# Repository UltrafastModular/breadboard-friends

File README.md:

breadboard-friends
==================

A collection of cute breakout boards riding solderless breadboards, mostly for analog audio works

These PCB layouts and schematics are released under a Creative Commons cc-by-sa
3.0 license.

Original design by émilie gillet
Design revisions by Gareth Johnson
Converted to KiCad and further revision by Nathan Schenk

NOTE: This is a forked version of breadboard-friends and adds two addition BBFs, one using Thonkiconn 3.5mm Jacks (bbf-thonkjacks) and another providing eurorack header with polarity protection for providing eurorack power to your breadboard from euro bus (bbf-europower).
NOTE: This version converts the project from Eagle to KiCad and footprint updates to jacks, including oval holes

BBF-EUROPOWER Bill Of Materials (BOM)

- 2x 200ma PTC Poly Fuse or equivalent (or jumper wires if no fuse is required);
- 2x 10uF 25V Electrolytic Caps;
- 2x 1N5818 diodes or equivalent;
- 2x Ferrite Beads;
- 4x 10 Pin DIL male headers.

BBF-THONKJACKS Bill Of Materials (BOM)

- 4x Thonkiconn Jacks;
- 1x 8 pin SIL female header;
- 2x 10 pin DIL male headers.

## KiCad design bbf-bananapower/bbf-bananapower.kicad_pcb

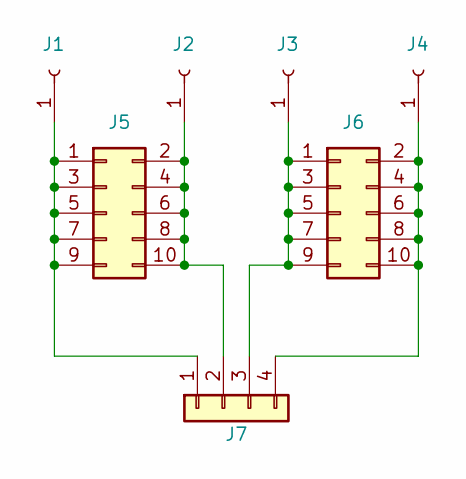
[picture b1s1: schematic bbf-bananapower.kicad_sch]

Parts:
J1, J2, J3, J4: Conn_01x01_Female; Banana_Cliff_S16N-PC
J5, J6: Conn_02x05_Counter_Clockwise; PinSocket_2x05_P2.54mm_Vertical
J7: Conn_01x04; PinSocket_1x04_P2.54mm_Vertical

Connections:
unnamed: J1.1, J5.1, J5.3, J5.5, J5.7, J5.9, J7.1
unnamed: J2.1, J5.2, J5.4, J5.6, J5.8, J5.10, J7.2
unnamed: J3.1, J6.1, J6.3, J6.5, J6.7, J6.9, J7.3
unnamed: J4.1, J6.2, J6.4, J6.6, J6.8, J6.10, J7.4

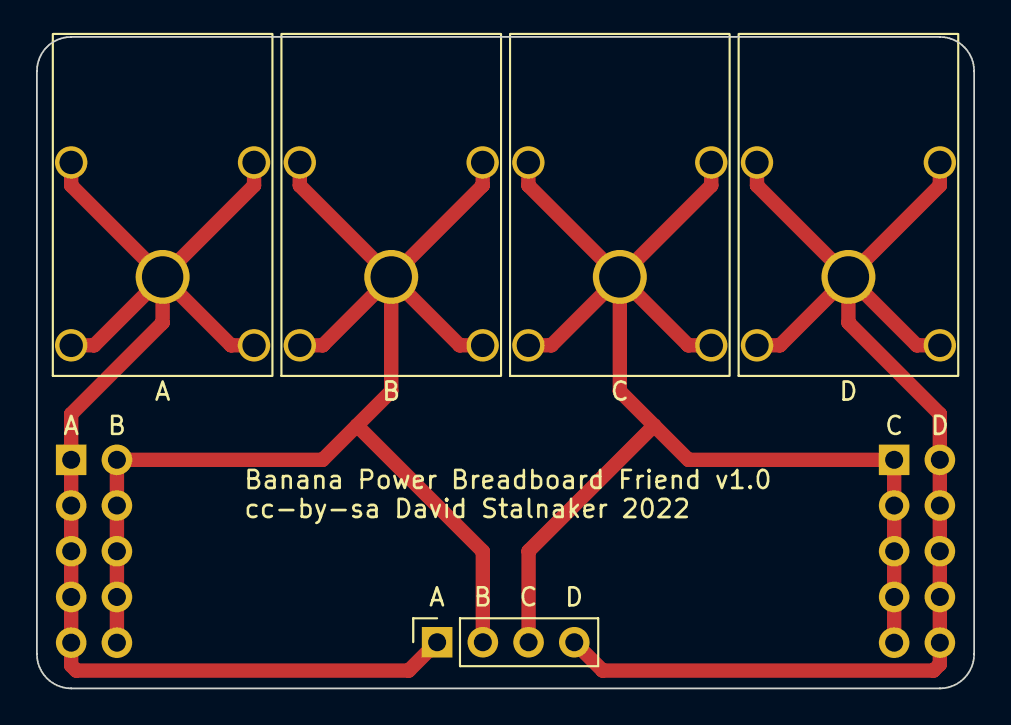
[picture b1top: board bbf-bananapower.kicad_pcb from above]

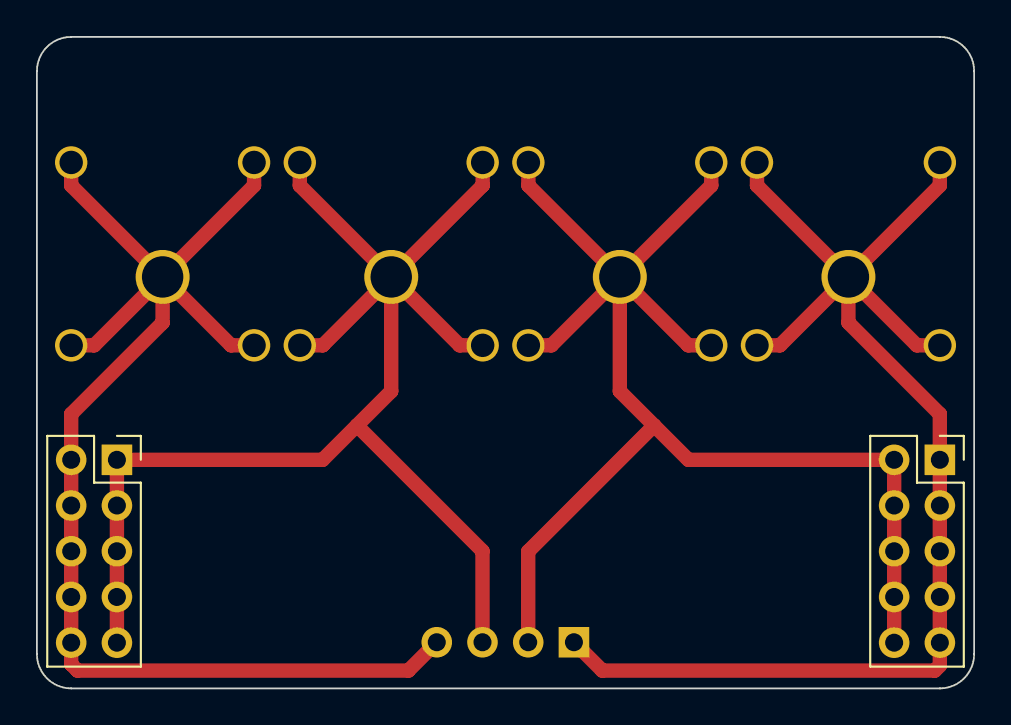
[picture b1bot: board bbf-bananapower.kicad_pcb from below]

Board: 2 copper layers, 52.1 x 36.2 mm, 7 parts (2 on the bottom side), 4 nets.

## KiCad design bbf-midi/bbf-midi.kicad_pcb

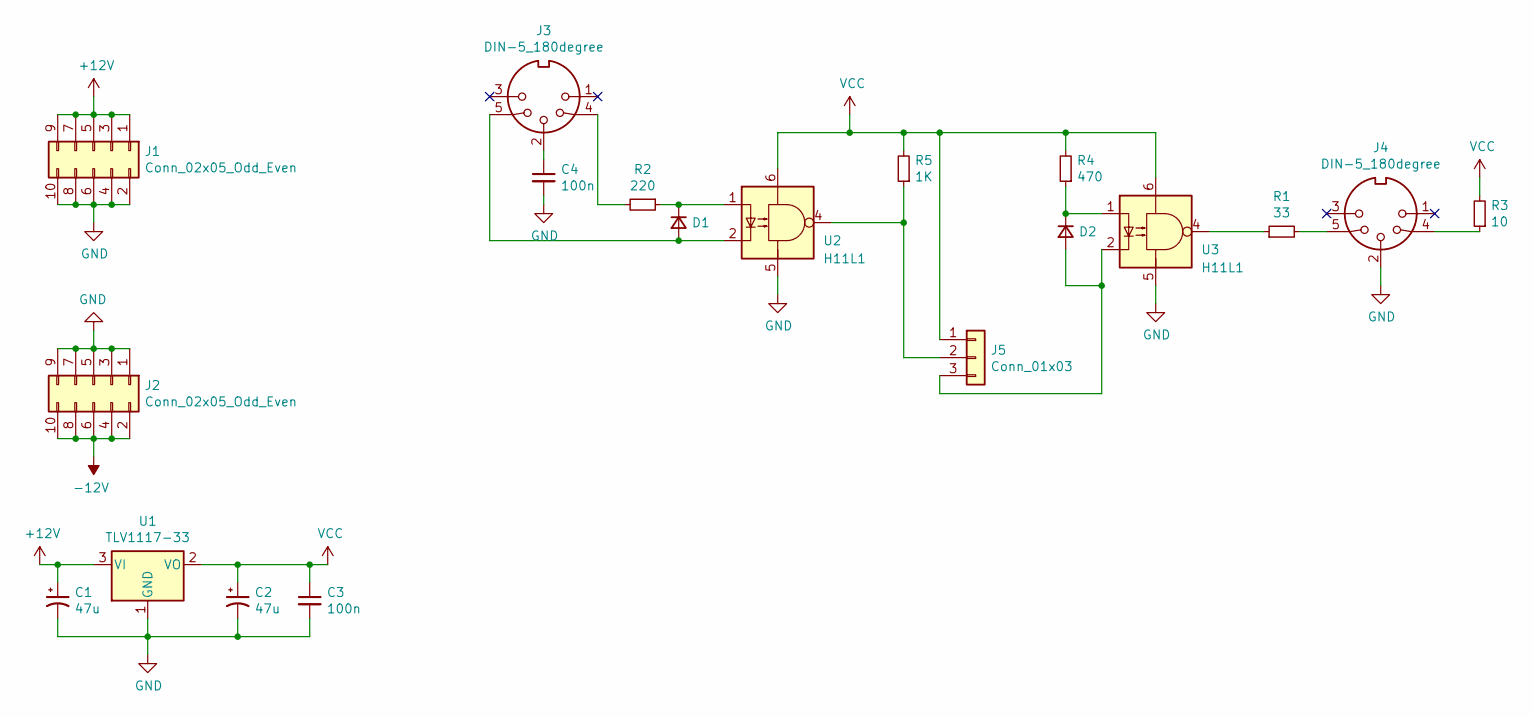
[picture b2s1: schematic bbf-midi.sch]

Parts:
C1, C2: 47u; CP_Radial_D5.0mm_P2.50mm
C3, C4: 100n; C_Disc_D3.0mm_W2.0mm_P2.50mm
D1, D2: D_Small; D_DO-35_SOD27_P7.62mm_Horizontal
J1, J2: Conn_02x05_Odd_Even; PinHeader_2x05_P2.54mm_Vertical
J3, J4: DIN-5_180degree; DIN_5_CUI_SDF-50J
J5: Conn_01x03; PinSocket_1x03_P2.54mm_Vertical
R1: 33; R_Axial_DIN0207_L6.3mm_D2.5mm_P7.62mm_Horizontal
R2: 220; R_Axial_DIN0207_L6.3mm_D2.5mm_P7.62mm_Horizontal
R3: 10; R_Axial_DIN0207_L6.3mm_D2.5mm_P7.62mm_Horizontal
R4: 470; R_Axial_DIN0207_L6.3mm_D2.5mm_P7.62mm_Horizontal
R5: 1K; R_Axial_DIN0207_L6.3mm_D2.5mm_P7.62mm_Horizontal
U1: TLV1117-33; TO-220-3_Vertical
U2, U3: H11L1; DIP-6_W7.62mm_Socket

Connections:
+12V: C1.1, J1.1, J1.3, J1.5, J1.7, J1.9, U1.3 (VI)
-12V: J2.2, J2.4, J2.6, J2.8, J2.10
GND: C1.2, C2.2, C3.2, C4.2, J1.2, J1.4, J1.6, J1.8, J1.10, J2.1, J2.3, J2.5, J2.7, J2.9, J4.2, U1.1 (GND), U2.5, U3.5
unnamed: C4.1, J3.2
unnamed: D1.1 (K), R2.1, U2.1
unnamed: D1.2 (A), J3.5, U2.2
unnamed: D2.1 (K), R4.1, U3.1
unnamed: D2.2 (A), J5.3, U3.2
unnamed: J3.4, R2.2
unnamed: J4.4, R3.1
unnamed: J4.5, R1.2
unnamed: J5.2, R5.1, U2.4
unnamed: R1.1, U3.4
VCC: C2.1, C3.1, J5.1, R3.2, R4.2, R5.2, U1.2 (VO), U2.6, U3.6

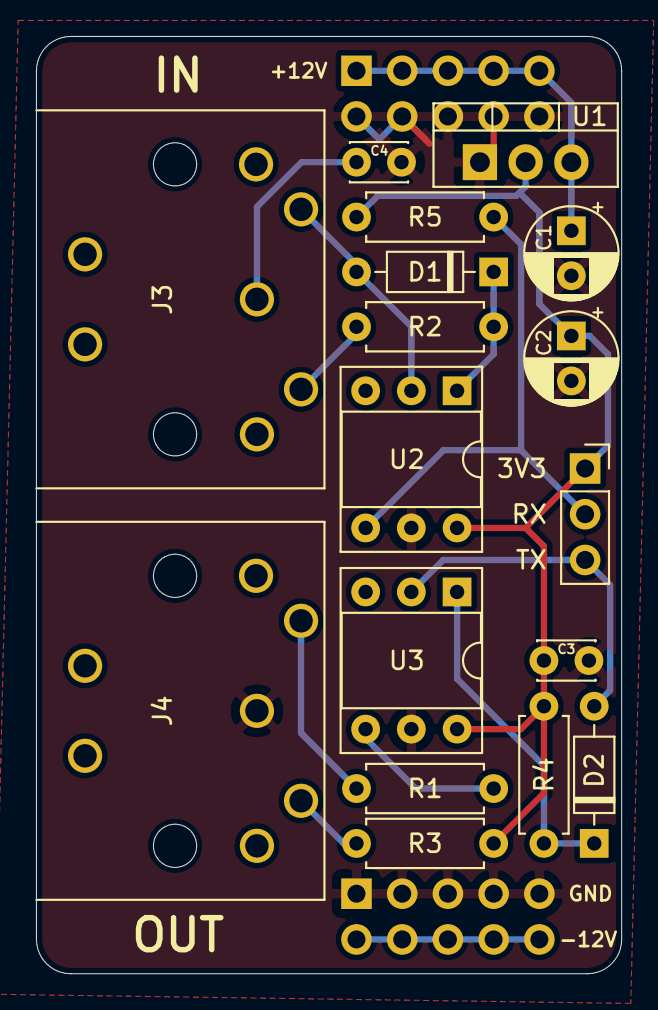
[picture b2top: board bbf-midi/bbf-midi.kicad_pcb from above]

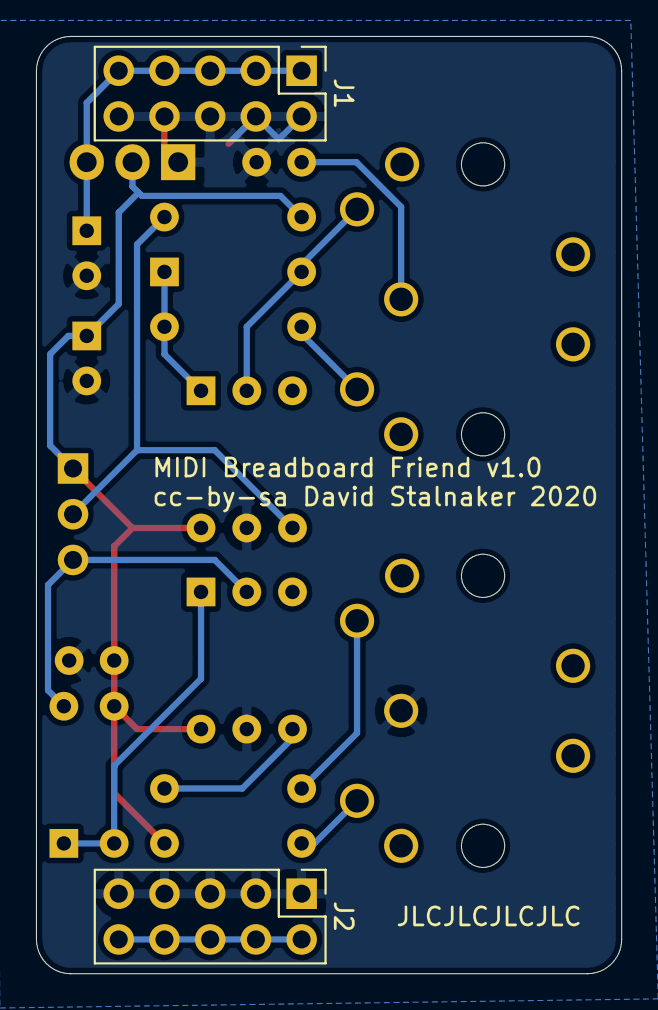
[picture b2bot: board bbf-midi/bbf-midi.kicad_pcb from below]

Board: 2 copper layers, 32.5 x 52.1 mm, 19 parts (2 on the bottom side), 14 nets.

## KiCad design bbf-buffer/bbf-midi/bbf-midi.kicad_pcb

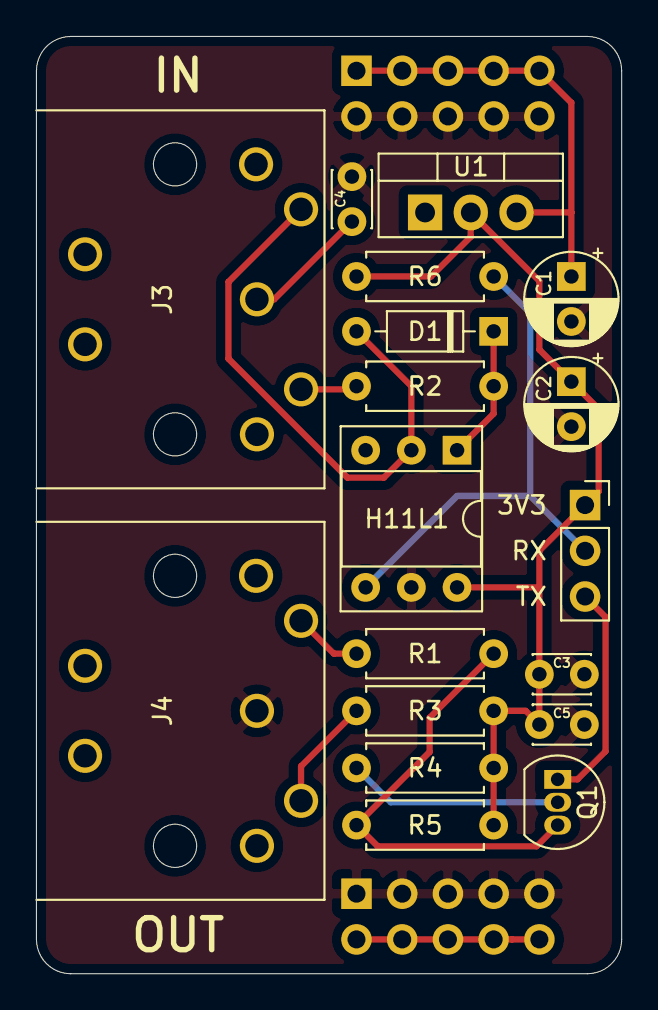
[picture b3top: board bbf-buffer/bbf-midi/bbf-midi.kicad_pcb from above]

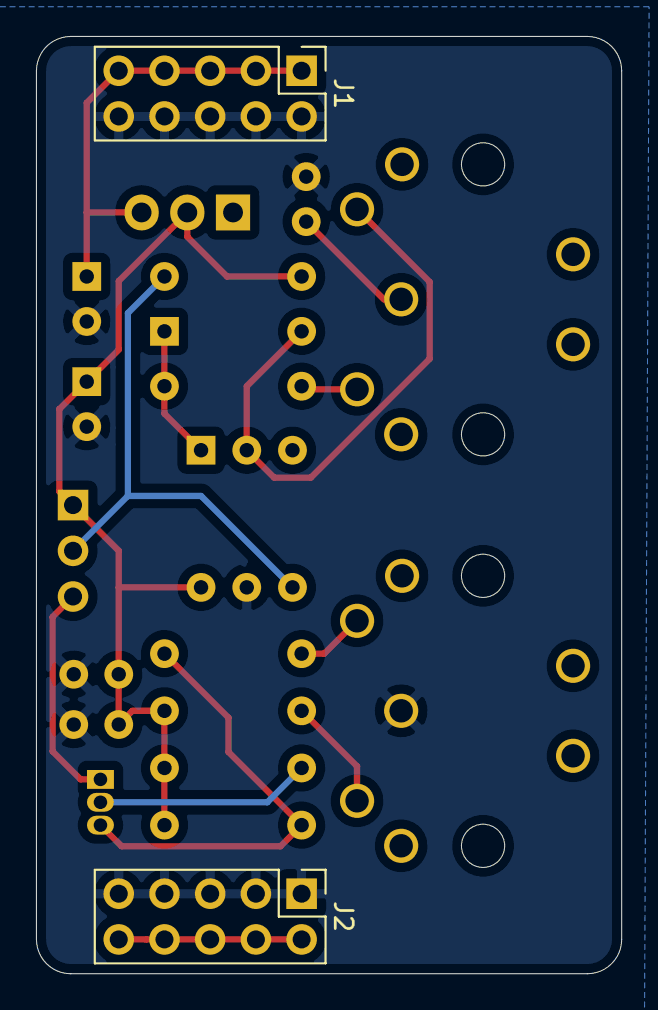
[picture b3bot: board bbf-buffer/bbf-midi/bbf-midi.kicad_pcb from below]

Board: 2 copper layers, 32.5 x 52.1 mm, 20 parts (2 on the bottom side), 14 nets.

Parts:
C1, C2: 47u; CP_Radial_D5.0mm_P2.50mm
C3, C4, C5: 100n; C_Disc_D3.0mm_W2.0mm_P2.50mm
D1: D_Small; D_DO-35_SOD27_P7.62mm_Horizontal
H11L1: H11L1; DIP-6_W7.62mm_Socket
J1, J2: Conn_02x05_Odd_Even; PinHeader_2x05_P2.54mm_Vertical
J3, J4: DIN-5_180degree; DIN_5_CUI_SDF-50J
J5: Conn_01x03; PinSocket_1x03_P2.54mm_Vertical
Q1: 2N3904; TO-92_Inline
R1: 33; R_Axial_DIN0207_L6.3mm_D2.5mm_P7.62mm_Horizontal
R2: 220; R_Axial_DIN0207_L6.3mm_D2.5mm_P7.62mm_Horizontal
R3: 10; R_Axial_DIN0207_L6.3mm_D2.5mm_P7.62mm_Horizontal
R4, R5, R6: 1K; R_Axial_DIN0207_L6.3mm_D2.5mm_P7.62mm_Horizontal
U1: TLV1117-33; TO-220-3_Vertical

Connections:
+12V: C1.1, J1.1, J1.3, J1.5, J1.7, J1.9, U1.3
-12V: J2.2, J2.4, J2.6, J2.8, J2.10
GND: C1.2, C2.2, C3.2, C4.2, C5.2, H11L1.5, J1.2, J1.4, J1.6, J1.8, J1.10, J2.1, J2.3, J2.5, J2.7, J2.9, J4.2
unnamed: C4.1, J3.2
unnamed: D1.1, H11L1.1, R2.1
unnamed: D1.2, H11L1.2, J3.5
unnamed: J3.4, R2.2
unnamed: J4.4, R3.1
unnamed: J4.5, R1.1
unnamed: H11L1.4, J5.2, R6.1
unnamed: J5.3, Q1.1
unnamed: Q1.2, R4.1
unnamed: Q1.3, R1.2, R5.1
VCC: C2.1, C3.1, C5.1, H11L1.6, J5.1, R3.2, R4.2, R5.2, R6.2, U1.2

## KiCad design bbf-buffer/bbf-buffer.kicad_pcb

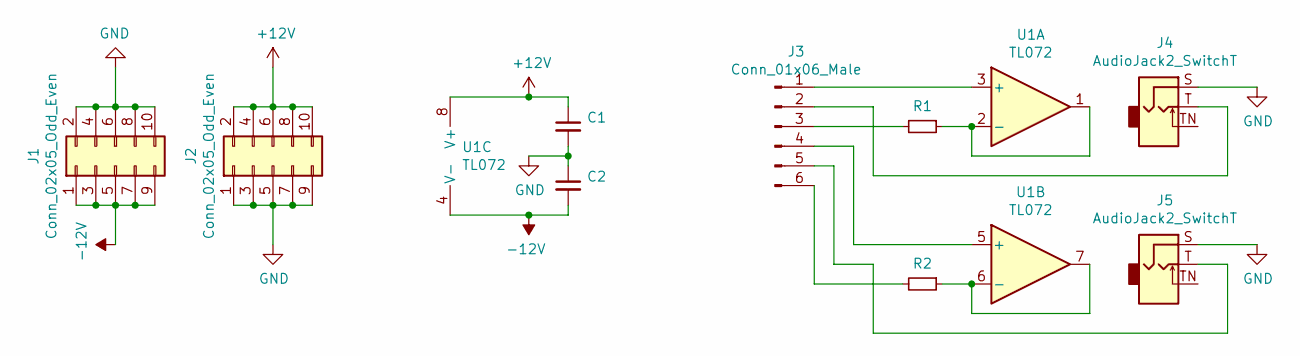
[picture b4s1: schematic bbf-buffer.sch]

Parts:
C1, C2: C_Small; C_Disc_D3.0mm_W1.6mm_P2.50mm
J1, J2: Conn_02x05_Odd_Even; PinHeader_2x05_P2.54mm_Vertical
J3: Conn_01x06_Male; PinHeader_1x06_P2.54mm_Vertical
J4, J5: AudioJack2_SwitchT; Thonkiconn_Tight
R1, R2: R_Small; R_Axial_DIN0207_L6.3mm_D2.5mm_P7.62mm_Horizontal
U1: TL072; DIP-8_W7.62mm_Socket

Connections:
+12V: C1.1, J2.2, J2.4, J2.6, J2.8, J2.10, U1.8 (V+); also elsewhere on the board
-12V: C2.2, J1.1, J1.3, J1.5, J1.7, J1.9, U1.4 (V-); also elsewhere on the board
GND: C1.2, C2.1, J1.2, J1.4, J1.6, J1.8, J1.10, J2.1, J2.3, J2.5, J2.7, J2.9, J4.S, J5.S
unnamed 3: J3.1, U1.3 (+); also elsewhere on the board
unnamed: J3.2, J4.T
unnamed: J3.3, R1.2
unnamed 6: J3.4, U1.5 (+); also elsewhere on the board
unnamed: J3.5, J5.T
unnamed: J3.6, R2.2
unnamed 9: R1.1, U1.1, U1.2 (-); also elsewhere on the board
unnamed 10: R2.1, U1.6 (-), U1.7; also elsewhere on the board

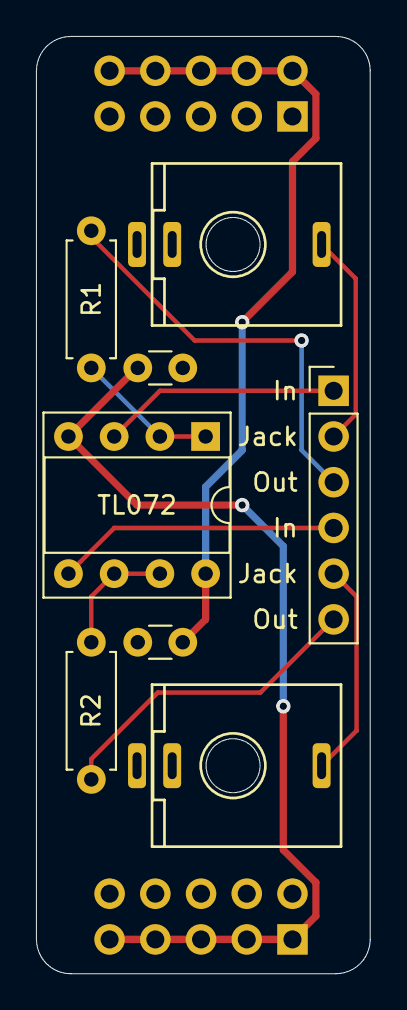
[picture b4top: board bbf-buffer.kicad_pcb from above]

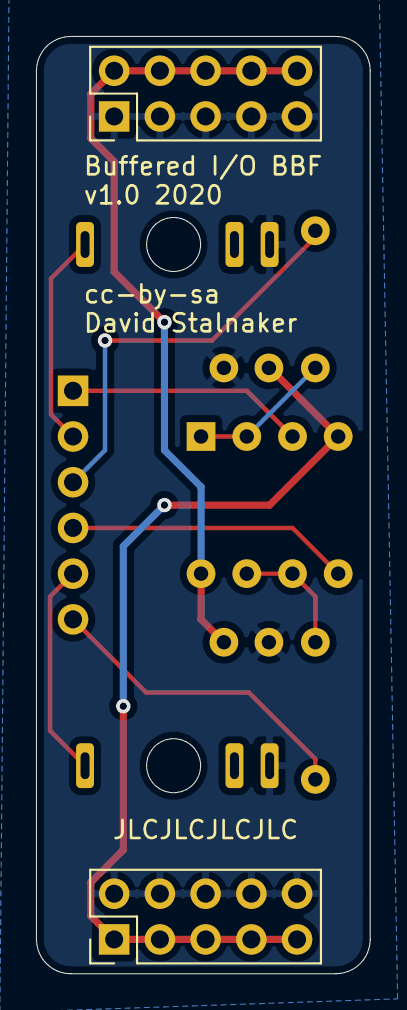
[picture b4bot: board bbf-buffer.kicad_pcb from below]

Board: 2 copper layers, 18.5 x 52.1 mm, 10 parts (2 on the bottom side), 11 nets.

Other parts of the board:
TL072: TL072; DIP-8_W7.62mm_Socket

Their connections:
+12V: TL072.8; also elsewhere on the board
-12V: TL072.4; also elsewhere on the board
unnamed 3: TL072.3; also elsewhere on the board
unnamed 6: TL072.5; also elsewhere on the board
unnamed 9: TL072.1, TL072.2; also elsewhere on the board
unnamed 10: TL072.6, TL072.7; also elsewhere on the board

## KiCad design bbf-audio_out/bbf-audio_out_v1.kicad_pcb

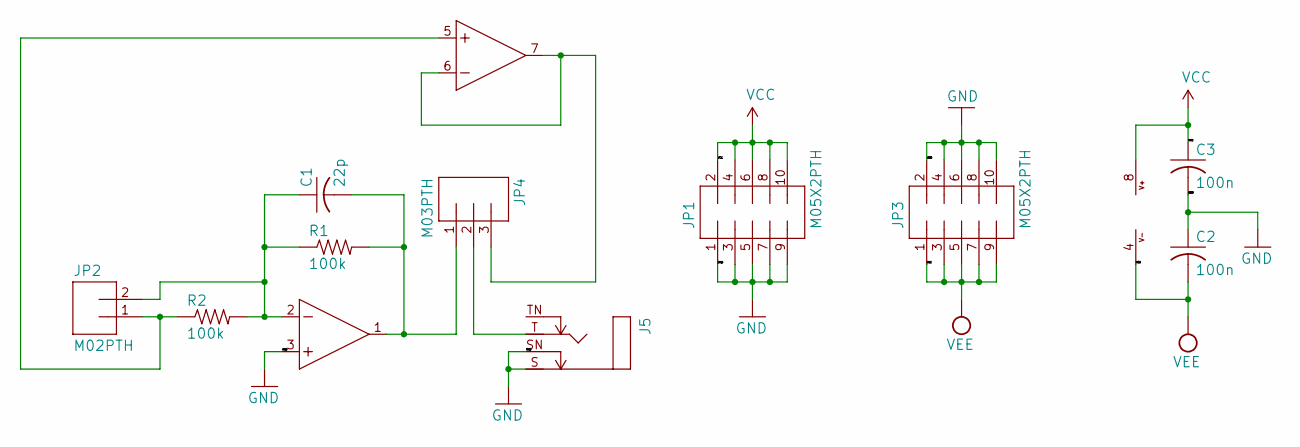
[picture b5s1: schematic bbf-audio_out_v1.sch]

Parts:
C1: 22p; C025-025X050
C2, C3: 100n; C025-025X050
IC1: TL072P; DIL08
J5: MONOSWSLIM; NRJ4HF
JP1, JP3: M05X2PTH; AVR_ICSP
JP2: M02PTH; 1X02
JP4: M03PTH; 1X03
R1, R2: 100k; 0204_7

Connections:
GND: C2.1, C3.2, IC1.3 (+IN), J5.S, J5.SN, JP1.1, JP1.3, JP1.5, JP1.7, JP1.9, JP3.2, JP3.4, JP3.6, JP3.8, JP3.10
unnamed: C1.1, IC1.2 (-IN), JP2.2, R1.1, R2.2
unnamed: C1.2, IC1.1 (OUT), JP4.1, R1.2
unnamed: IC1.5 (+IN), JP2.1, R2.1
unnamed: IC1.6 (-IN), IC1.7 (OUT), JP4.3
unnamed: J5.T, JP4.2
VCC: C3.1, IC1.8 (V+), JP1.2, JP1.4, JP1.6, JP1.8, JP1.10
VEE: C2.2, IC1.4 (V-), JP3.1, JP3.3, JP3.5, JP3.7, JP3.9

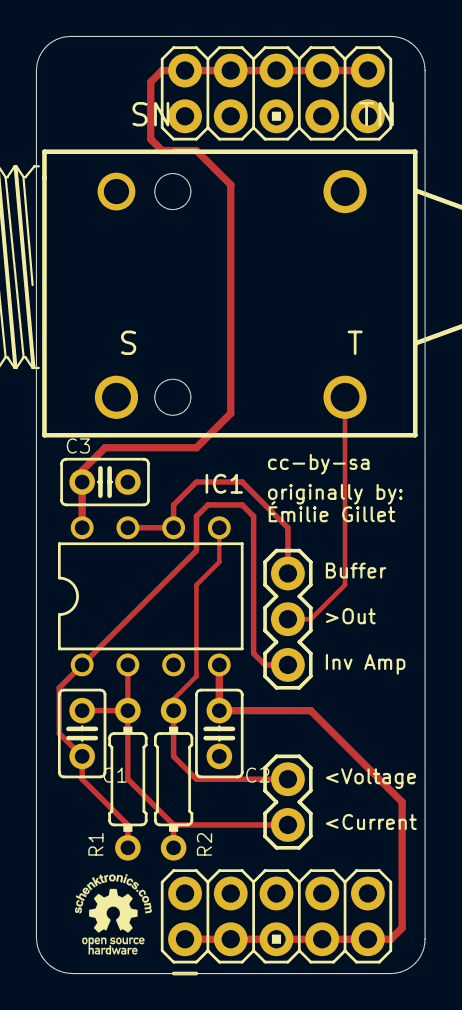
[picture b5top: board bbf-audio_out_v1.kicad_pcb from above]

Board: 2 copper layers, 21.6 x 52.1 mm, 11 parts (0 on the bottom side), 8 nets.

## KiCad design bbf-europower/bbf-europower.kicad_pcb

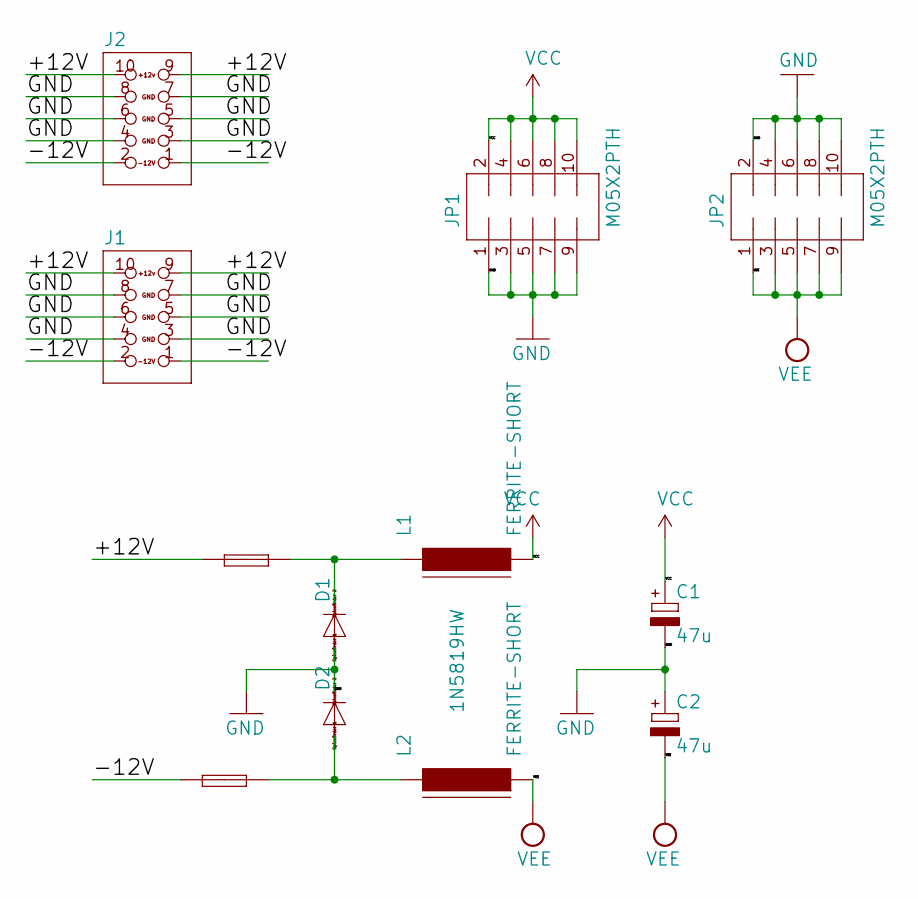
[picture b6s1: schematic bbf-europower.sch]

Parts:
+FUSE1: +FUSE; C050H075X075
-FUSE1: -FUSE; C050H075X075
C1, C2: 47u; E2-5
D1, D2: 1N5819HW; DO35-7
J1, J2: CON_HEADER_2X05-PTH; M2X5
JP1, JP2: M05X2PTH; AVR_ICSP
L1, L2: FERRITE-SHORT; FBS

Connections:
/+12V: +FUSE1.1, J1.9, J1.10, J2.9, J2.10
/-12V: -FUSE1.1, J1.1, J1.2, J2.1, J2.2
GND: C1.-, C2.+, D1.A, D2.C, J1.3, J1.4, J1.5, J1.6, J1.7, J1.8, J2.3, J2.4, J2.5, J2.6, J2.7, J2.8, JP1.1, JP1.3, JP1.5, JP1.7, JP1.9, JP2.2, JP2.4, JP2.6, JP2.8, JP2.10
unnamed: +FUSE1.2, D1.C, L1.1
unnamed: -FUSE1.2, D2.A, L2.1
VCC: C1.+, JP1.2, JP1.4, JP1.6, JP1.8, JP1.10, L1.2
VEE: C2.-, JP2.1, JP2.3, JP2.5, JP2.7, JP2.9, L2.2

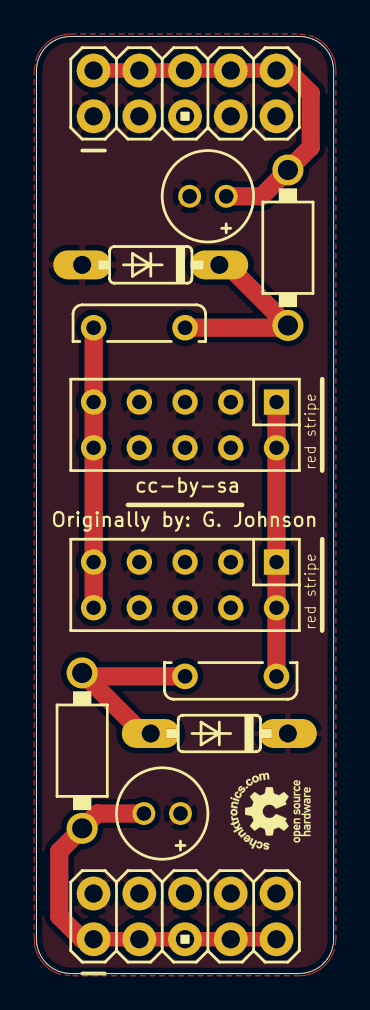
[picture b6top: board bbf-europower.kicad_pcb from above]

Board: 2 copper layers, 16.5 x 52.1 mm, 12 parts (0 on the bottom side), 7 nets.

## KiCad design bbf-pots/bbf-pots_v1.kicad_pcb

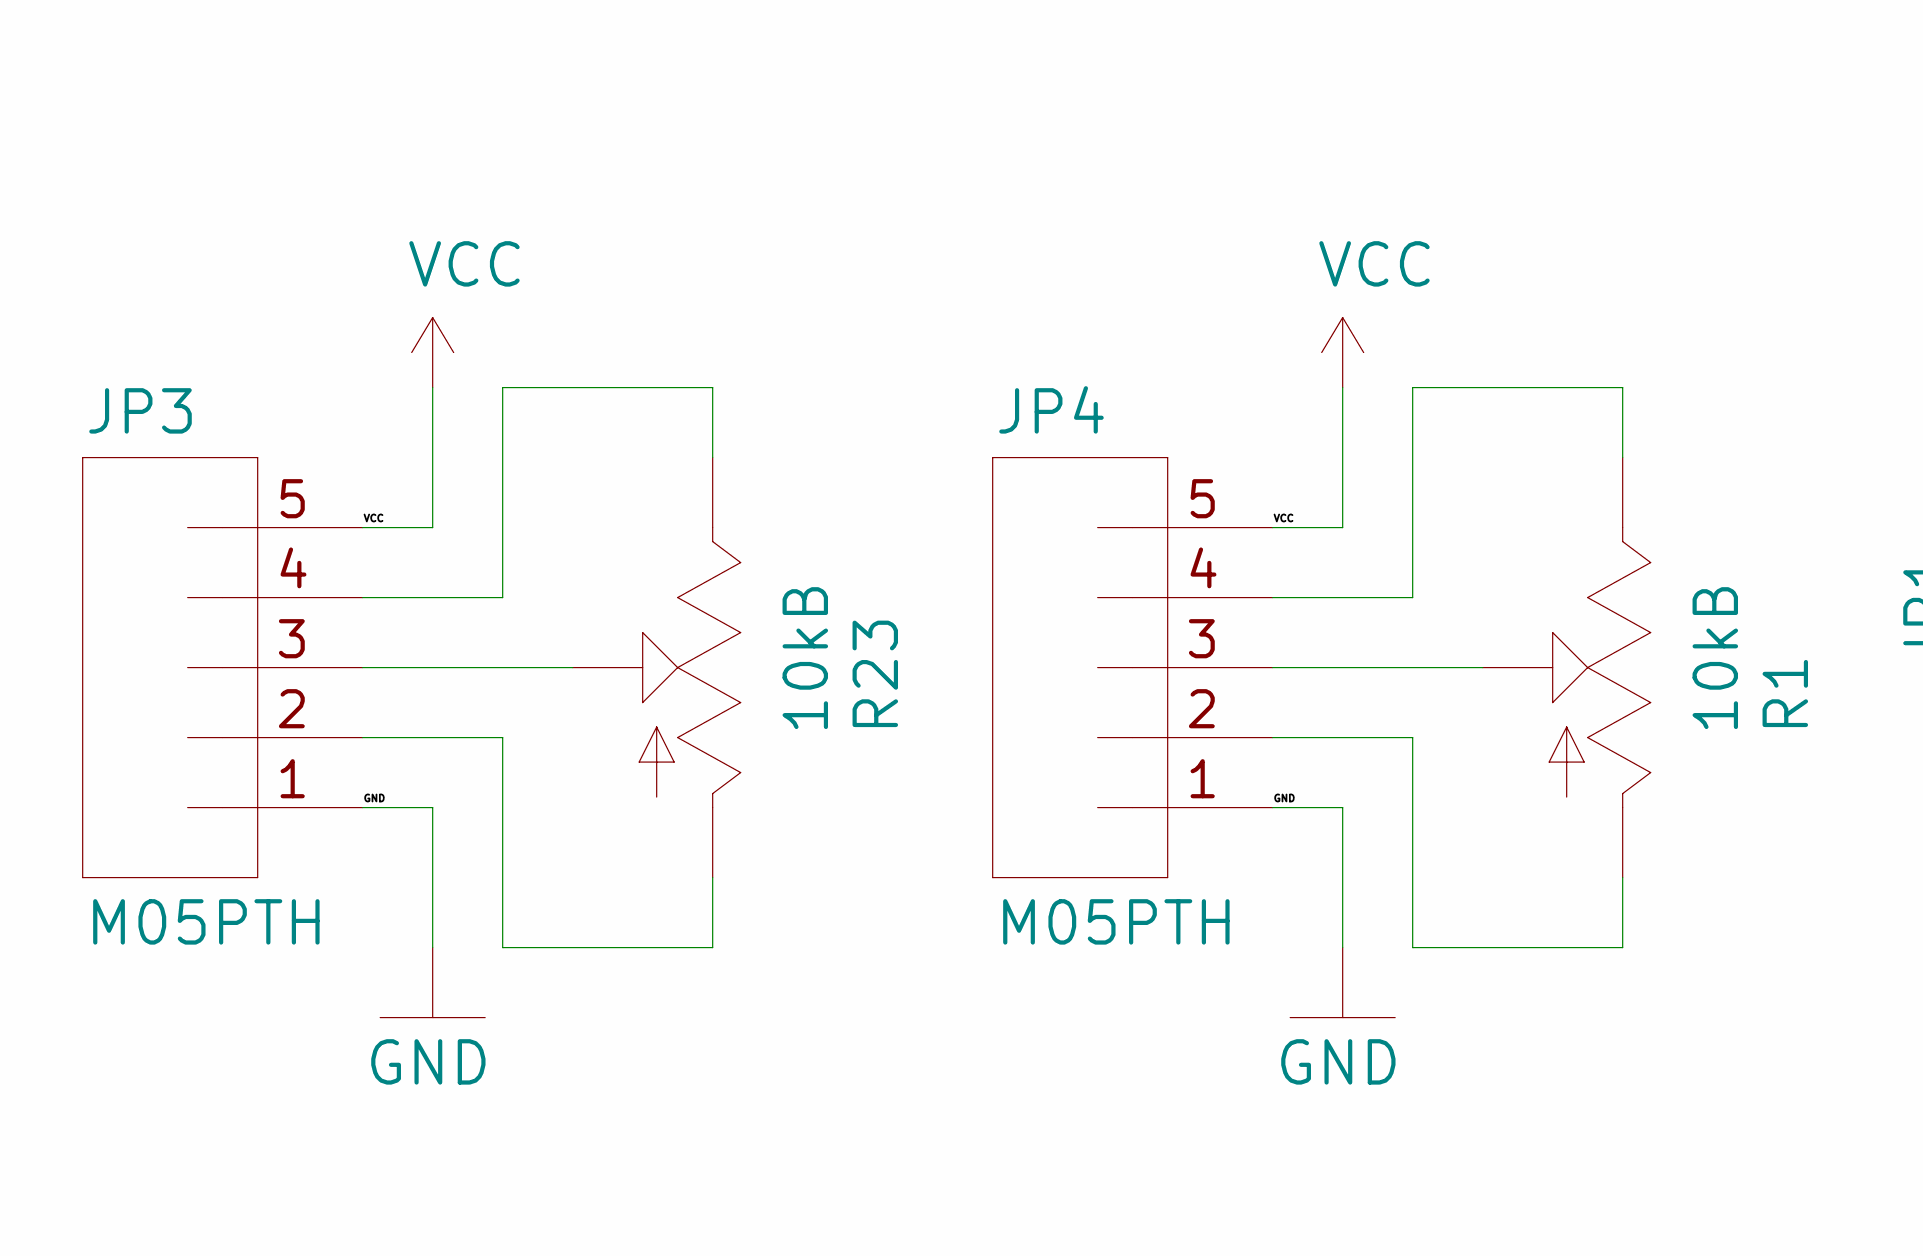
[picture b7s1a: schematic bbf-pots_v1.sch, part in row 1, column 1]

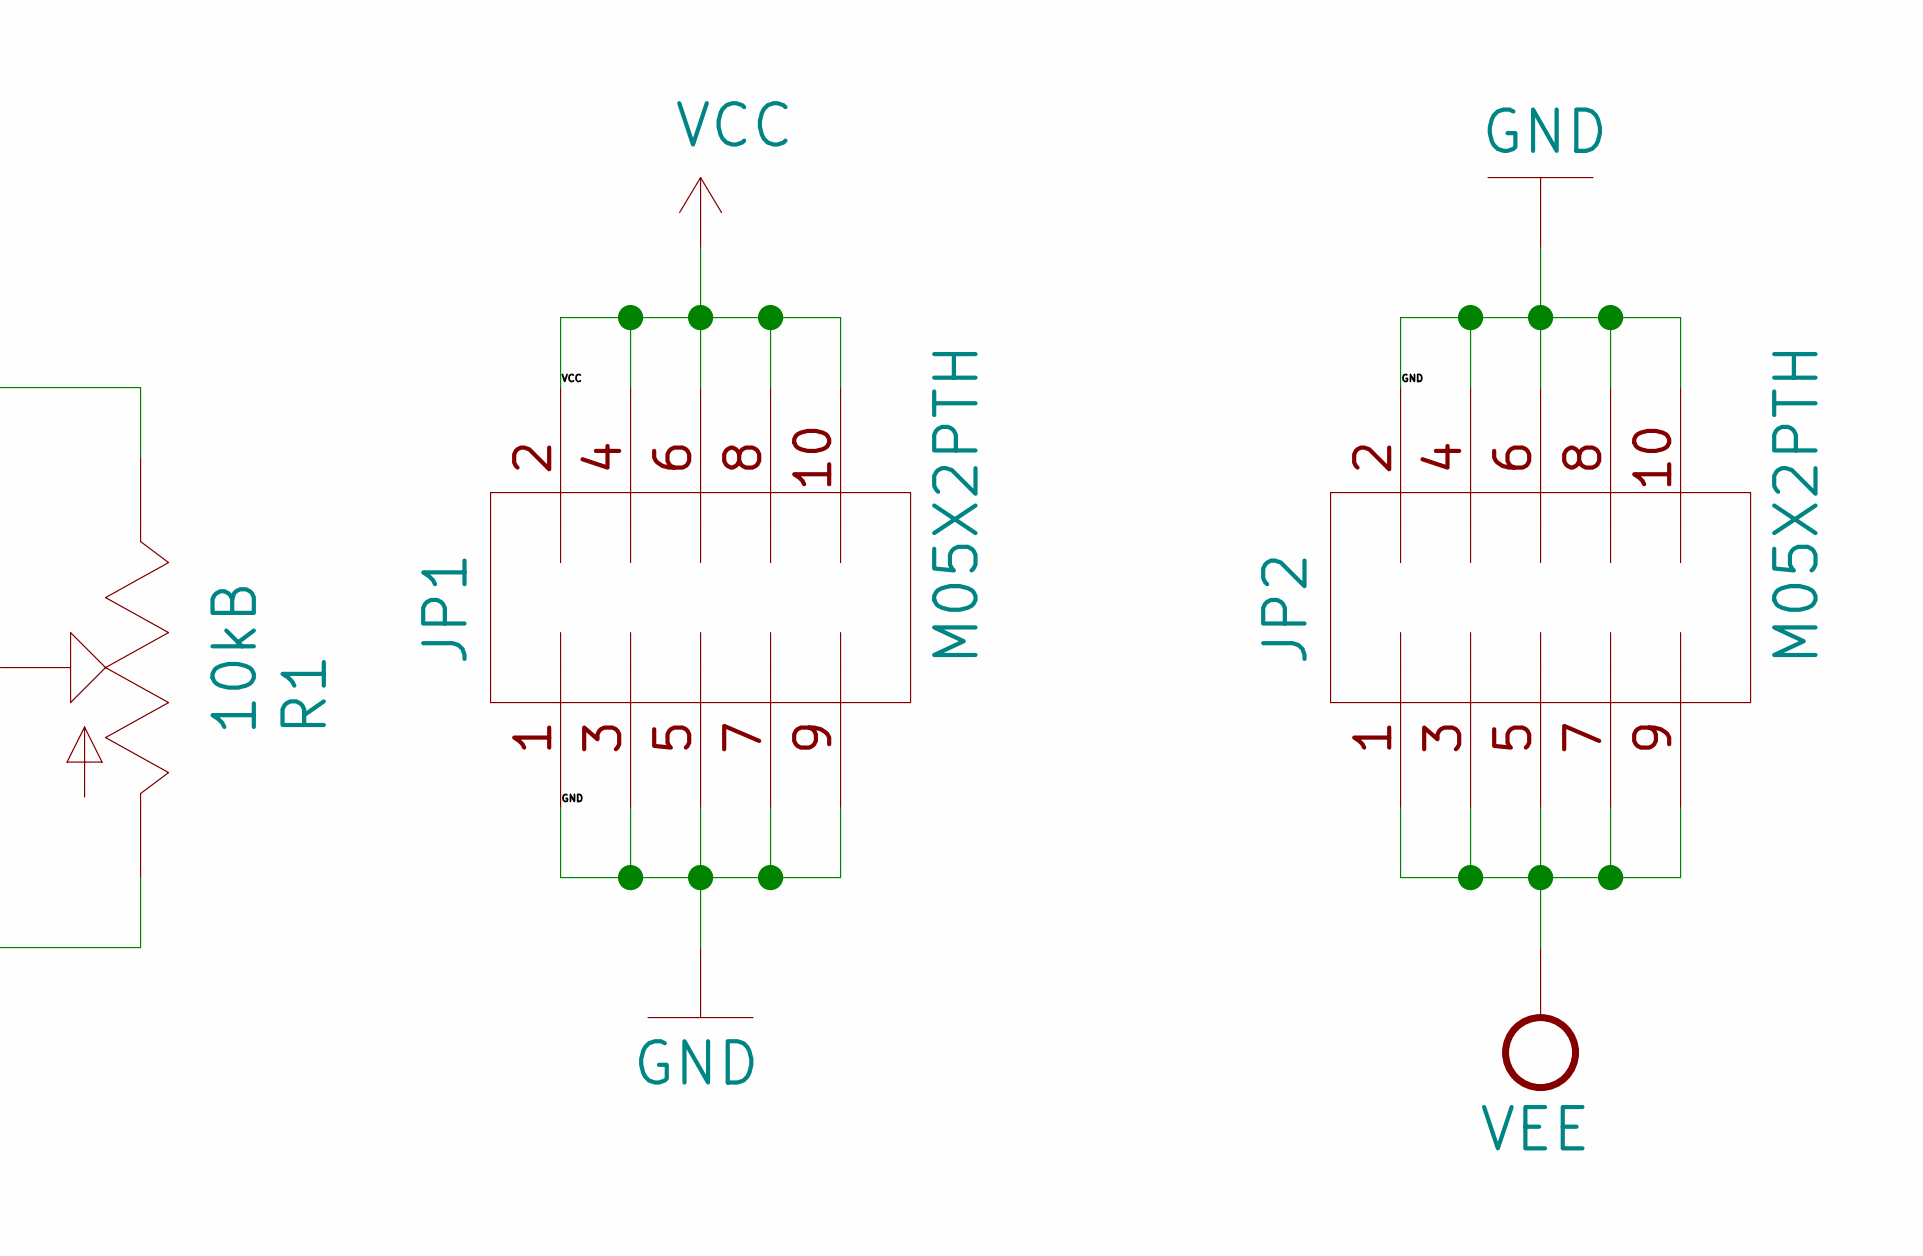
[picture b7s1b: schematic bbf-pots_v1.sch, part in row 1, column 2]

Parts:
JP1, JP2: M05X2PTH; AVR_ICSP
JP3, JP4: M05PTH; 1X05
R1, R23: 10kB; ALPS_POT_VERTICAL

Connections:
GND: JP1.1, JP1.3, JP1.5, JP1.7, JP1.9, JP2.2, JP2.4, JP2.6, JP2.8, JP2.10, JP3.1, JP4.1
unnamed: JP3.2, R23.P$3 (A)
unnamed: JP3.3, R23.P$2 (S)
unnamed: JP3.4, R23.P$1 (E)
unnamed: JP4.2, R1.P$3 (A)
unnamed: JP4.3, R1.P$2 (S)
unnamed: JP4.4, R1.P$1 (E)
VCC: JP1.2, JP1.4, JP1.6, JP1.8, JP1.10, JP3.5, JP4.5
VEE: JP2.1, JP2.3, JP2.5, JP2.7, JP2.9

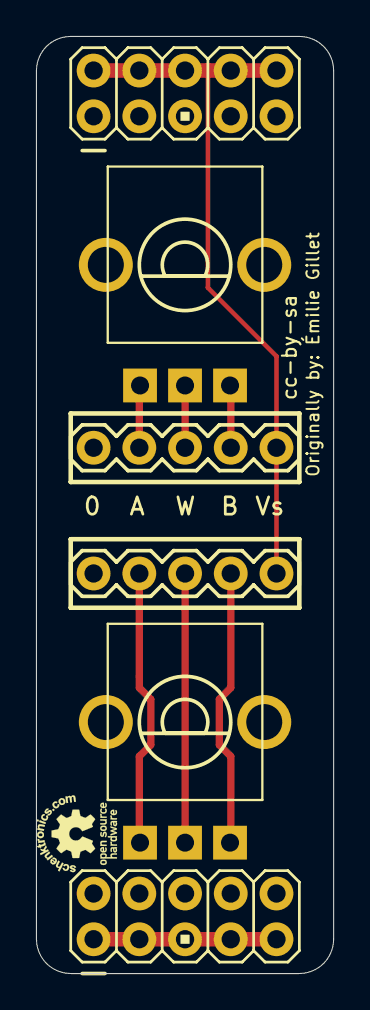
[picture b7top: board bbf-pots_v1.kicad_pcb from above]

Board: 2 copper layers, 16.5 x 52.1 mm, 6 parts (0 on the bottom side), 9 nets.

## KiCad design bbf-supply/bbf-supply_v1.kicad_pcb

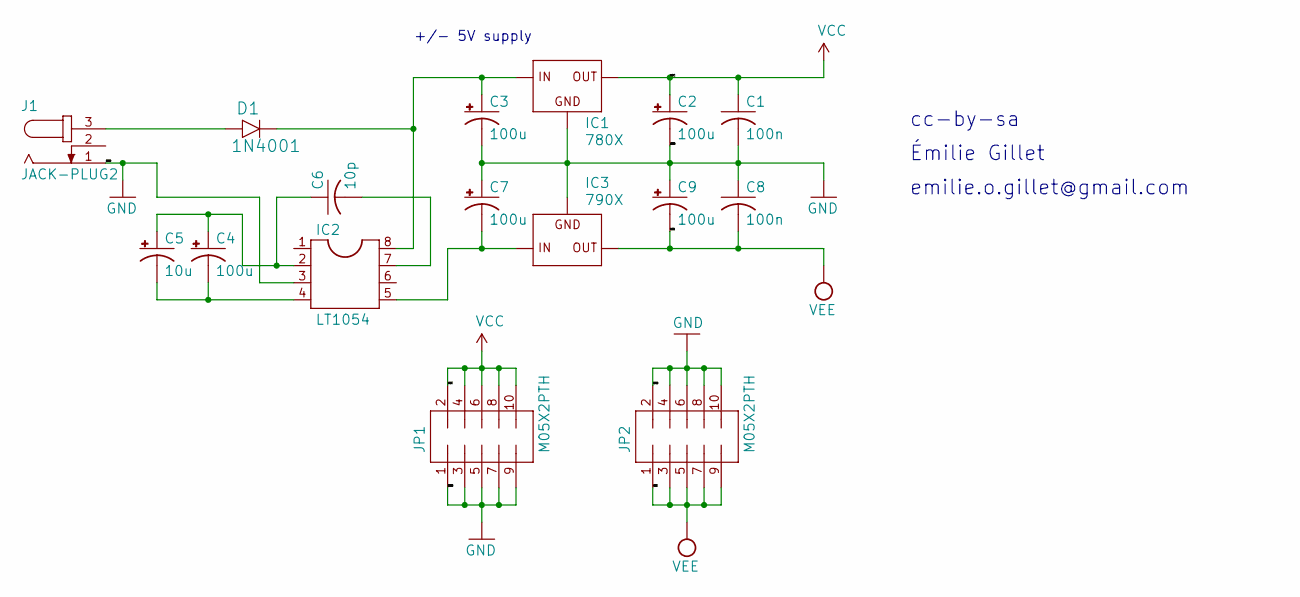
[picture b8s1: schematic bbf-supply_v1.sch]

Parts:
C1, C8: 100n; C025-025X050
C2, C3, C7, C9: 100u; E2,5-7
C4: 100u; E2,5-6
C5: 10u; E2,5-5
C6: 10p; C025-025X050
D1: 1N4001; DO41-3
IC1: 780X; 78XXS
IC2: LT1054; DIL08
IC3: 790X; 79XXS
J1: JACK-PLUG2; SPC4078_BIG_HOLES
JP1, JP2: M05X2PTH; AVR_ICSP

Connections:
GND: C1.2, C2.-, C3.-, C7.+, C8.1, C9.+, IC1.GND, IC2.3, IC3.GND, J1.1, JP1.1, JP1.3, JP1.5, JP1.7, JP1.9, JP2.2, JP2.4, JP2.6, JP2.8, JP2.10
unnamed: C3.+, D1.C, IC1.IN, IC2.8
unnamed: C4.+, C5.+, C6.1, IC2.2
unnamed: C4.-, C5.-, IC2.4
unnamed: C6.2, IC2.7
unnamed: C7.-, IC2.5, IC3.IN
unnamed: D1.A, J1.3
VCC: C1.1, C2.+, IC1.OUT, JP1.2, JP1.4, JP1.6, JP1.8, JP1.10
VEE: C8.2, C9.-, IC3.OUT, JP2.1, JP2.3, JP2.5, JP2.7, JP2.9

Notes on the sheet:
cc-by-sa
Émilie Gillet
emilie.o.gillet@gmail.com
+/- 5V supply

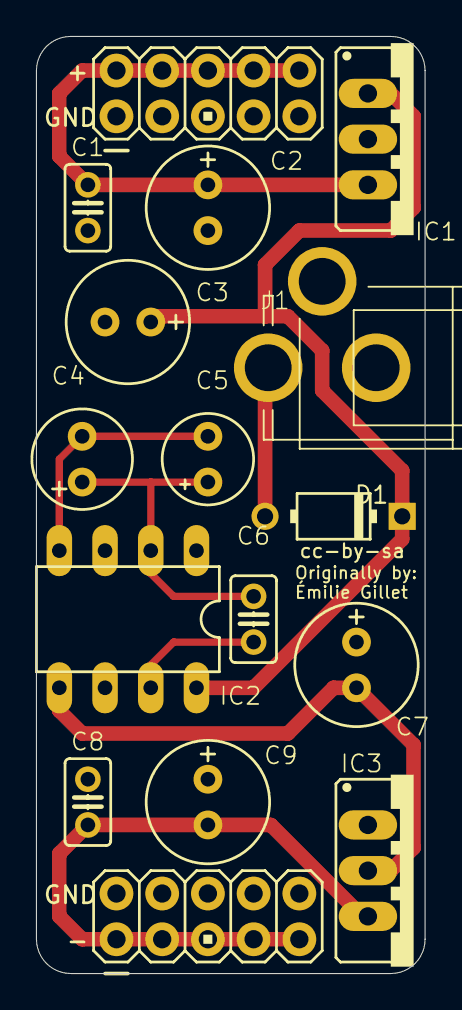
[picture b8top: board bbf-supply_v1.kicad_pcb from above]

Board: 2 copper layers, 21.6 x 52.1 mm, 16 parts (0 on the bottom side), 9 nets.

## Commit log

2020-03-15 Convert to KiCad
2020-03-15 generate bbf-audio_out gerbers
2020-03-15 Change bbf-eurojacks to oval jack holes
2020-03-15 Update jack footprint
2020-03-15 Create bbf-eurojacks gerbers
2020-03-15 generate bbf-europower gerbers
2020-03-15 Generate bbf-pots gerbers
2020-03-15 add bbf-pots Gerbers.zip
2020-03-15 generate bbf-supply gerbers
2020-03-15 Update bbf-thonkjacks jack footprint
2020-03-15 Generate gerbers for bbf-thonkjacks
2020-03-15 Update Readme.md
    Add Logos
    Update attribution
2020-03-15 Update bbf-audio-out Gerbers
2020-08-10 Add buffered I/O breadboard friend.
2020-08-18 Add midi breadboard friend.
2020-08-29 Ignore KiCAD autosave/backup junk.
2020-08-29 Update midi friend to 3.3v, including RX buffer.
2020-08-29 Move midi friend to the top level.
2020-08-31 Fix some small mistakes in the midi friend.
2022-02-22 Added banana power friend.

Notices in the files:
bbf-bananapower/bbf-bananapower.kicad_pcb:
cc-by-sa David Stalnaker 2022
bbf-midi/bbf-midi.kicad_pcb:
cc-by-sa David Stalnaker 2020
